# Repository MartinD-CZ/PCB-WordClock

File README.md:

# Simple PCB tabletop WordClock
*A relatively simple-to-make 100x100 mm WordClock made from 3 PCBs*

See [this article](http://embedblog.eu/?p=636) on my blog for more info.

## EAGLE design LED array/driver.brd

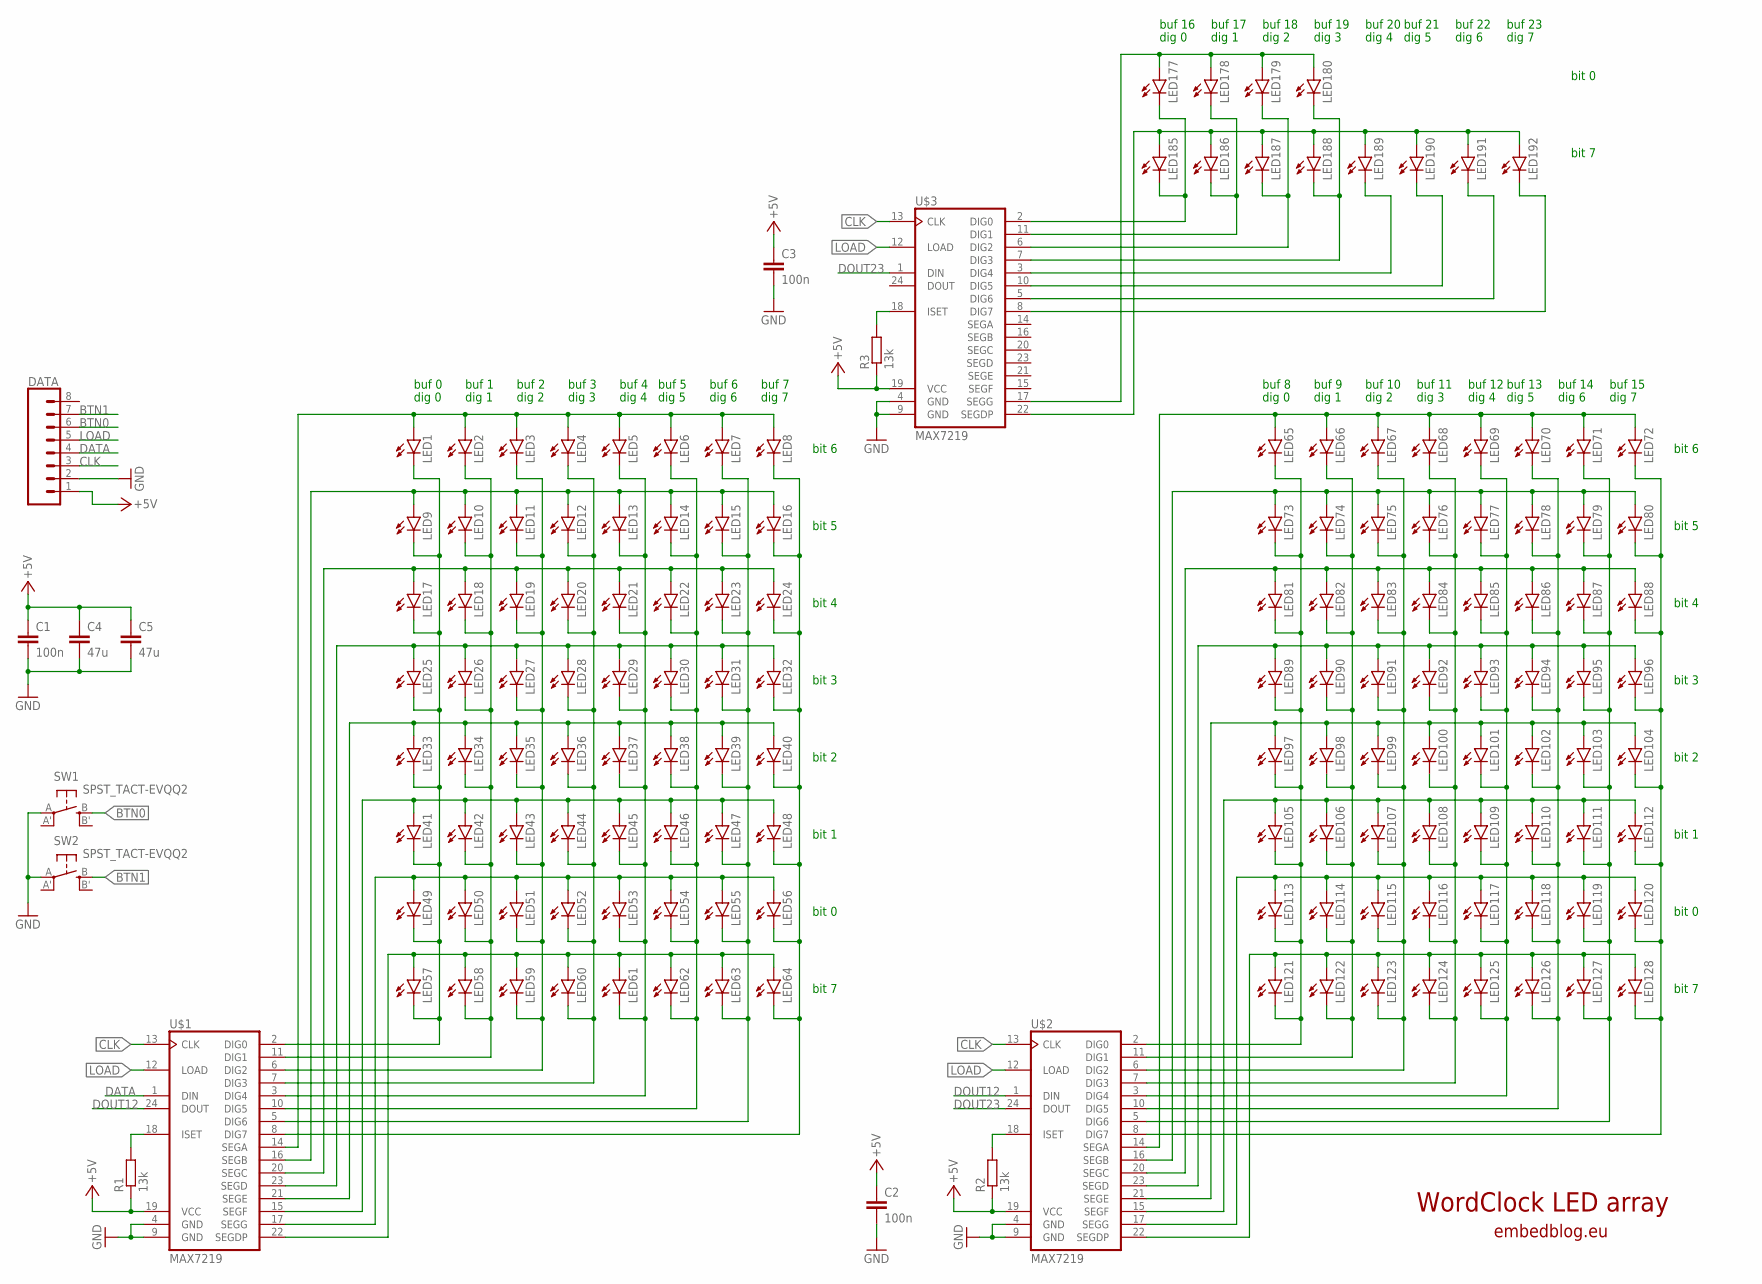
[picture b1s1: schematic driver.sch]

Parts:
C1, C2, C3: 100n; C1206
C4, C5: 47u; C1206
DATA: CONN_08"; 1X08
LED1, LED2, LED3, LED4, LED5, LED6, LED7, LED8, LED9, LED10, LED11, LED12, LED13, LED14, LED15, LED16, LED17, LED18, LED19, LED20, LED21, LED22, LED23, LED24, LED25, LED26, LED27, LED28, LED29, LED30, LED31, LED32, LED33, LED34, LED35, LED36, LED37, LED38, LED39, LED40, LED41, LED42, LED43, LED44, LED45, LED46, LED47, LED48, LED49, LED50, LED51, LED52, LED53, LED54, LED55, LED56, LED57, LED58, LED59, LED60, LED61, LED62, LED63, LED64, LED65, LED66, LED67, LED68, LED69, LED70, LED71, LED72, LED73, LED74, LED75, LED76, LED77, LED78, LED79, LED80, LED81, LED82, LED83, LED84, LED85, LED86, LED87, LED88, LED89, LED90, LED91, LED92, LED93, LED94, LED95, LED96, LED97, LED98, LED99, LED100, LED101, LED102, LED103, LED104, LED105, LED106, LED107, LED108, LED109, LED110, LED111, LED112, LED113, LED114, LED115, LED116, LED117, LED118, LED119, LED120, LED121, LED122, LED123, LED124, LED125, LED126, LED127, LED128, LED177, LED178, LED179, LED180, LED185, LED186, LED187, LED188, LED189, LED190, LED191, LED192: LEDCHIPLED_1206; CHIPLED_1206
R1, R2, R3: 13k; R1206
SW1, SW2: SPST_TACT-EVQQ2; EVQ-Q2
U$1, U$2, U$3: MAX7219; SO24W

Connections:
+5V: C1.1, C2.1, C3.1, C4.1, C5.1, DATA.1, R1.1, R2.1, R3.1, U$1.19 (VCC), U$2.19 (VCC), U$3.19 (VCC)
BTN0: DATA.6, SW1.B (S)
BTN1: DATA.7, SW2.B (S)
CLK: DATA.3, U$1.13 (CLK), U$2.13 (CLK), U$3.13 (CLK)
DATA: DATA.4, U$1.1 (DIN)
DOUT12: U$1.24 (DOUT), U$2.1 (DIN)
DOUT23: U$2.24 (DOUT), U$3.1 (DIN)
GND: C1.2, C2.2, C3.2, C4.2, C5.2, DATA.2, SW1.A, SW2.A, U$1.4 (GND), U$1.9 (GND), U$2.4 (GND), U$2.9 (GND), U$3.4 (GND), U$3.9 (GND)
LOAD: DATA.5, U$1.12 (LOAD), U$2.12 (LOAD), U$3.12 (LOAD)
unnamed: LED1.A, LED2.A, LED3.A, LED4.A, LED5.A, LED6.A, LED7.A, LED8.A, U$1.14 (SEGA)
unnamed: LED25.A, LED26.A, LED27.A, LED28.A, LED29.A, LED30.A, LED31.A, LED32.A, U$1.23 (SEGD)
unnamed: LED9.A, LED10.A, LED11.A, LED12.A, LED13.A, LED14.A, LED15.A, LED16.A, U$1.16 (SEGB)
unnamed: LED17.A, LED18.A, LED19.A, LED20.A, LED21.A, LED22.A, LED23.A, LED24.A, U$1.20 (SEGC)
unnamed: LED33.A, LED34.A, LED35.A, LED36.A, LED37.A, LED38.A, LED39.A, LED40.A, U$1.21 (SEGE)
unnamed: LED41.A, LED42.A, LED43.A, LED44.A, LED45.A, LED46.A, LED47.A, LED48.A, U$1.15 (SEGF)
unnamed: LED49.A, LED50.A, LED51.A, LED52.A, LED53.A, LED54.A, LED55.A, LED56.A, U$1.17 (SEGG)
unnamed: LED57.A, LED58.A, LED59.A, LED60.A, LED61.A, LED62.A, LED63.A, LED64.A, U$1.22 (SEGDP)
unnamed: LED1.C, LED9.C, LED17.C, LED25.C, LED33.C, LED41.C, LED49.C, LED57.C, U$1.2 (DIG0)
unnamed: R1.2, U$1.18 (ISET)
unnamed: LED65.A, LED66.A, LED67.A, LED68.A, LED69.A, LED70.A, LED71.A, LED72.A, U$2.14 (SEGA)
unnamed: LED73.A, LED74.A, LED75.A, LED76.A, LED77.A, LED78.A, LED79.A, LED80.A, U$2.16 (SEGB)
unnamed: LED81.A, LED82.A, LED83.A, LED84.A, LED85.A, LED86.A, LED87.A, LED88.A, U$2.20 (SEGC)
unnamed: LED89.A, LED90.A, LED91.A, LED92.A, LED93.A, LED94.A, LED95.A, LED96.A, U$2.23 (SEGD)
unnamed: LED97.A, LED98.A, LED99.A, LED100.A, LED101.A, LED102.A, LED103.A, LED104.A, U$2.21 (SEGE)
unnamed: LED105.A, LED106.A, LED107.A, LED108.A, LED109.A, LED110.A, LED111.A, LED112.A, U$2.15 (SEGF)
unnamed: LED2.C, LED10.C, LED18.C, LED26.C, LED34.C, LED42.C, LED50.C, LED58.C, U$1.11 (DIG1)
unnamed: LED113.A, LED114.A, LED115.A, LED116.A, LED117.A, LED118.A, LED119.A, LED120.A, U$2.17 (SEGG)
unnamed: LED121.A, LED122.A, LED123.A, LED124.A, LED125.A, LED126.A, LED127.A, LED128.A, U$2.22 (SEGDP)
unnamed: LED65.C, LED73.C, LED81.C, LED89.C, LED97.C, LED105.C, LED113.C, LED121.C, U$2.2 (DIG0)
unnamed: LED66.C, LED74.C, LED82.C, LED90.C, LED98.C, LED106.C, LED114.C, LED122.C, U$2.11 (DIG1)
unnamed: LED67.C, LED75.C, LED83.C, LED91.C, LED99.C, LED107.C, LED115.C, LED123.C, U$2.6 (DIG2)
unnamed: LED68.C, LED76.C, LED84.C, LED92.C, LED100.C, LED108.C, LED116.C, LED124.C, U$2.7 (DIG3)
unnamed: LED69.C, LED77.C, LED85.C, LED93.C, LED101.C, LED109.C, LED117.C, LED125.C, U$2.3 (DIG4)
unnamed: LED3.C, LED11.C, LED19.C, LED27.C, LED35.C, LED43.C, LED51.C, LED59.C, U$1.6 (DIG2)
unnamed: LED70.C, LED78.C, LED86.C, LED94.C, LED102.C, LED110.C, LED118.C, LED126.C, U$2.10 (DIG5)
unnamed: LED71.C, LED79.C, LED87.C, LED95.C, LED103.C, LED111.C, LED119.C, LED127.C, U$2.5 (DIG6)
unnamed: LED72.C, LED80.C, LED88.C, LED96.C, LED104.C, LED112.C, LED120.C, LED128.C, U$2.8 (DIG7)
unnamed: R2.2, U$2.18 (ISET)
unnamed: LED4.C, LED12.C, LED20.C, LED28.C, LED36.C, LED44.C, LED52.C, LED60.C, U$1.7 (DIG3)
unnamed: LED177.A, LED178.A, LED179.A, LED180.A, U$3.17 (SEGG)
unnamed: LED185.A, LED186.A, LED187.A, LED188.A, LED189.A, LED190.A, LED191.A, LED192.A, U$3.22 (SEGDP)
unnamed: LED177.C, LED185.C, U$3.2 (DIG0)
unnamed: LED178.C, LED186.C, U$3.11 (DIG1)
unnamed: LED5.C, LED13.C, LED21.C, LED29.C, LED37.C, LED45.C, LED53.C, LED61.C, U$1.3 (DIG4)
unnamed: LED179.C, LED187.C, U$3.6 (DIG2)
unnamed: LED180.C, LED188.C, U$3.7 (DIG3)
unnamed: LED189.C, U$3.3 (DIG4)
unnamed: LED190.C, U$3.10 (DIG5)
unnamed: LED191.C, U$3.5 (DIG6)
unnamed: LED192.C, U$3.8 (DIG7)
unnamed: R3.2, U$3.18 (ISET)
unnamed: LED6.C, LED14.C, LED22.C, LED30.C, LED38.C, LED46.C, LED54.C, LED62.C, U$1.10 (DIG5)
unnamed: LED7.C, LED15.C, LED23.C, LED31.C, LED39.C, LED47.C, LED55.C, LED63.C, U$1.5 (DIG6)
unnamed: LED8.C, LED16.C, LED24.C, LED32.C, LED40.C, LED48.C, LED56.C, LED64.C, U$1.8 (DIG7)

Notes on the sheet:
bit 0
bit 1
bit 2
bit 3
bit 4
bit 5
bit 6
bit 7
dig 0
dig 1
dig 2
dig 3
dig 4
dig 5
dig 6
dig 7
buf 0
buf 1
buf 2
buf 4
buf 5
buf 6
buf 7
buf 3
buf 8
buf 9
buf 10
buf 12
buf 13
buf 14
buf 15
buf 11
buf 16
buf 17
buf 18
buf 20
buf 21
buf 22
buf 23
buf 19

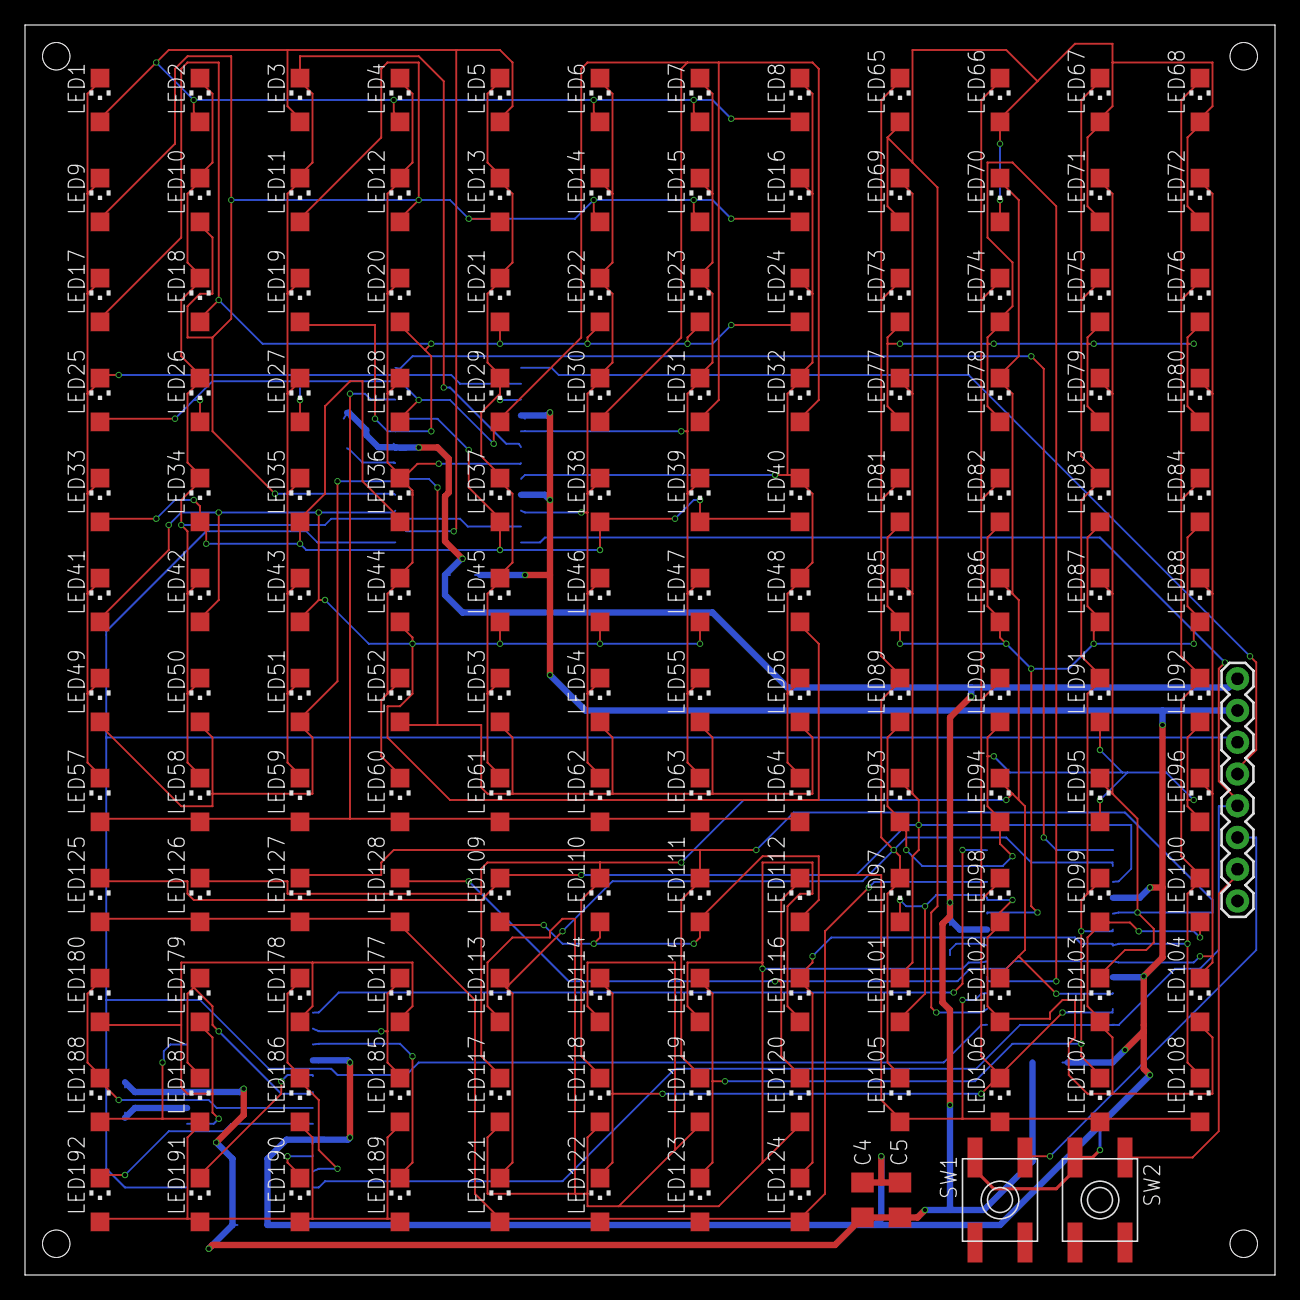
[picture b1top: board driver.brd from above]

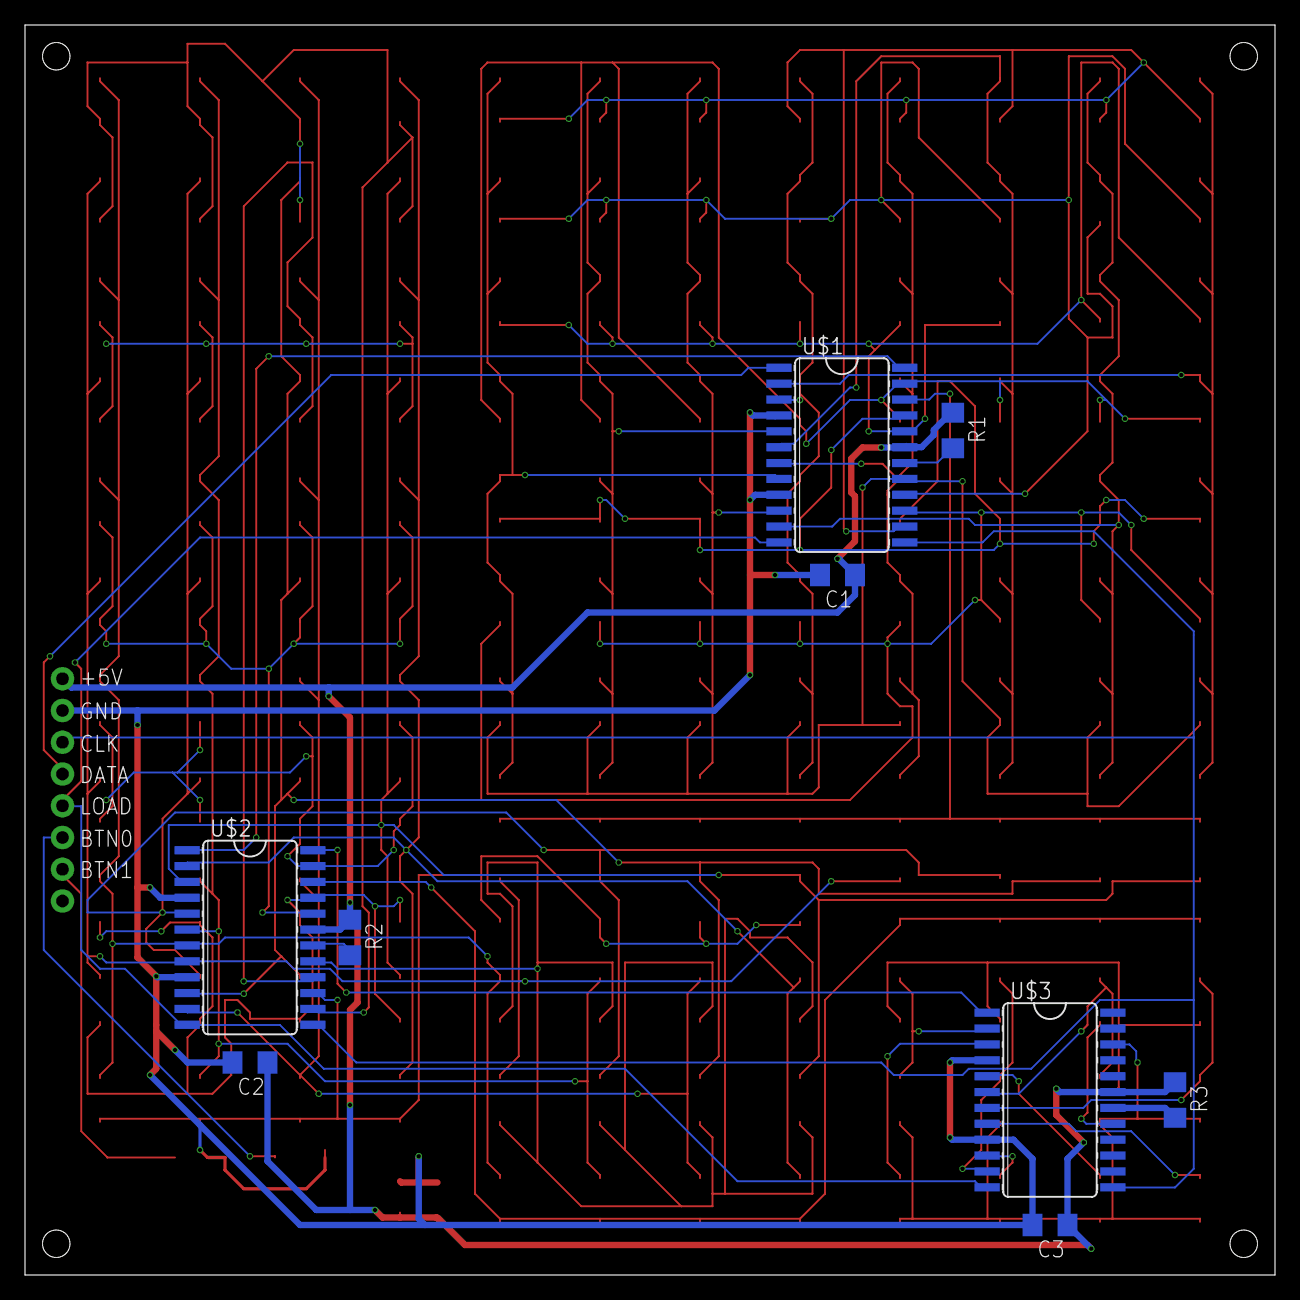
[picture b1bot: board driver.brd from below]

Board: 2 copper layers, 100.0 x 100.0 mm, 154 parts (9 on the bottom side), 54 nets.

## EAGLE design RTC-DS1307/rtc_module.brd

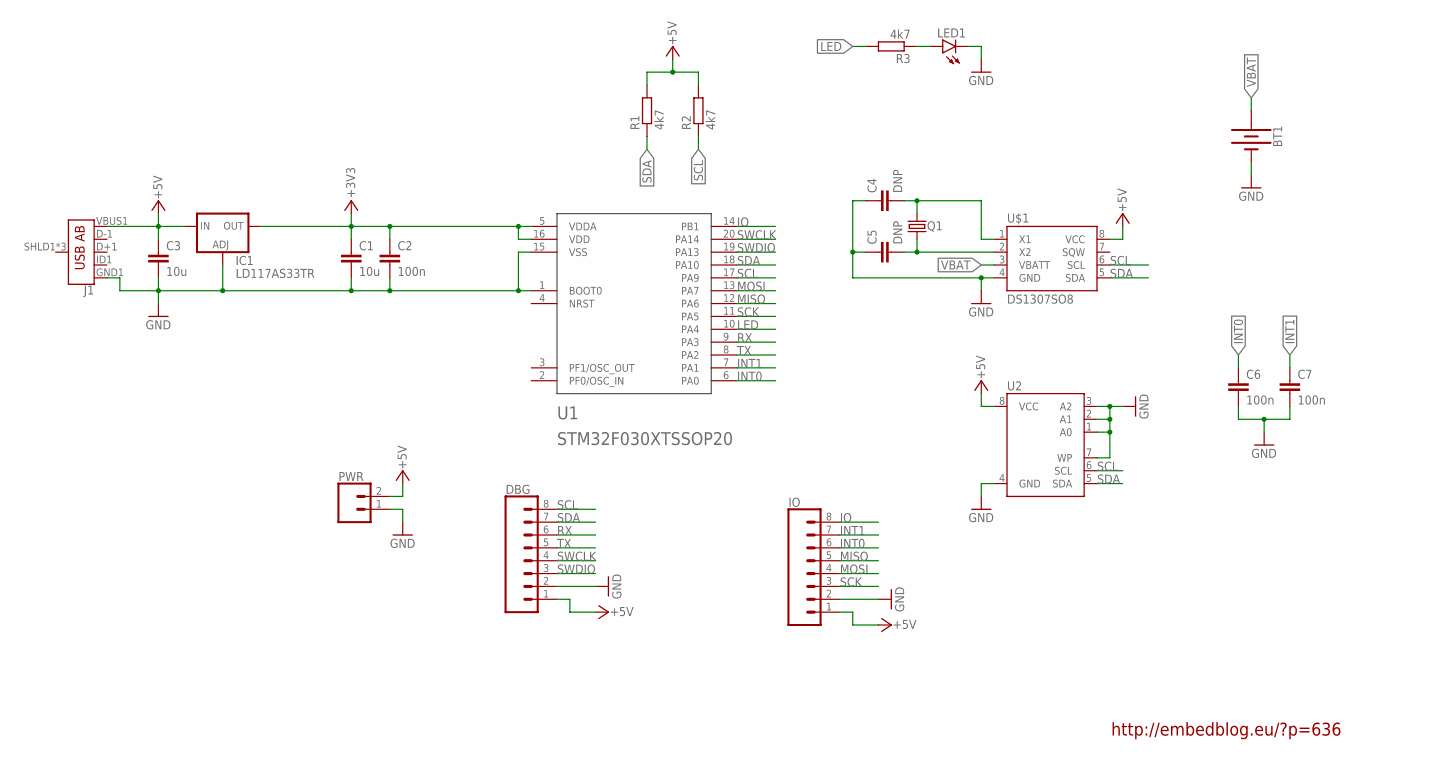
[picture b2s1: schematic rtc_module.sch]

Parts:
BT1: BATTERY-20MM_PTH; BATTCOM_20MM_PTH
C1, C3: 10u; C1206
C2, C6, C7: 100n; C1206
C4, C5: DNP; C1206
DBG: CONN_08"; 1X08
IC1: LD117AS33TR; SOT223
IO: CONN_08"; 1X08
J1: USB_AB_SMT; USB-AB-MICRO-SMD
LED1: LEDCHIPLED_1206; CHIPLED_1206
PWR: CONN_02PTH3; 1X02_LONGPADS
Q1: CRYSTALTC38H; TC38H
R1, R2, R3: 4k7; R1206
U1: STM32F030XTSSOP20; TSSOP-20
U2: 24LCXX; SOIC8
U$1: DS1307SO8; SO08

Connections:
+3V3: C1.1, C2.1, IC1.4 (OUT), U1.5 (VDDA), U1.16 (VDD)
+5V: C3.1, DBG.1, IC1.3 (IN), IO.1, J1.VBUS1 (VBUS), PWR.2, R1.2, R2.2, U2.8 (VCC), U$1.8 (VCC)
GND: BT1.2 (-), C1.2, C2.2, C3.2, C4.1, C5.1, C6.2, C7.2, DBG.2, IC1.1 (ADJ), IO.2, J1.GND1 (GND), LED1.C, PWR.1, U1.1 (BOOT0), U1.15 (VSS), U2.1 (A0), U2.2 (A1), U2.3 (A2), U2.4 (GND), U2.7 (WP), U$1.4 (GND)
INT0: C6.1, IO.6, U1.6 (PA0)
INT1: C7.1, IO.7, U1.7 (PA1)
IO: IO.8, U1.14 (PB1)
LED: R3.2, U1.10 (PA4)
MISO: IO.5, U1.12 (PA6)
MOSI: IO.4, U1.13 (PA7)
unnamed: C5.2, Q1.1, U$1.2 (X2)
unnamed: C4.2, Q1.2, U$1.1 (X1)
unnamed: LED1.A, R3.1
RX: DBG.6, U1.9 (PA3)
SCK: IO.3, U1.11 (PA5)
SCL: DBG.8, R2.1, U1.17 (PA9), U2.6 (SCL), U$1.6 (SCL)
SDA: DBG.7, R1.1, U1.18 (PA10), U2.5 (SDA), U$1.5 (SDA)
SWCLK: DBG.4, U1.20 (PA14)
SWDIO: DBG.3, U1.19 (PA13)
TX: DBG.5, U1.8 (PA2)
VBAT: BT1.1 (+), U$1.3 (VBATT)

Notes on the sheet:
http://embedblog.eu/?p=636

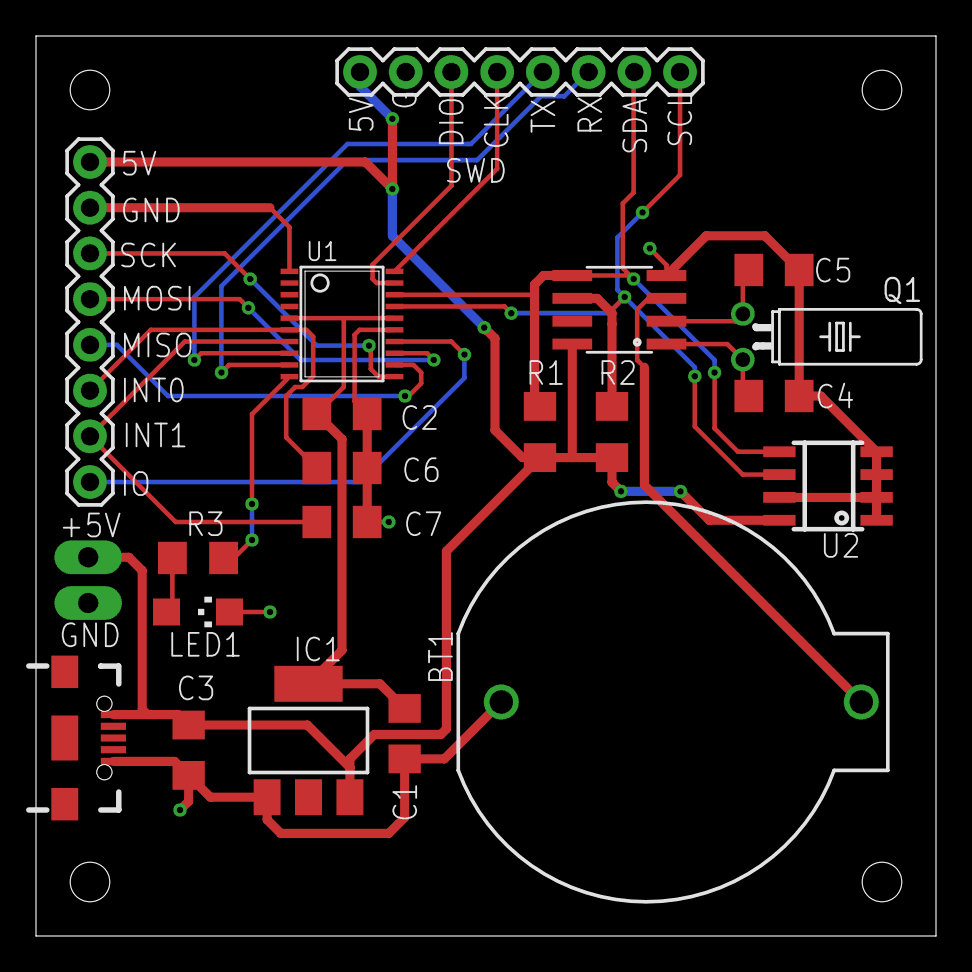
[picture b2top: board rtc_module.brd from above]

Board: 2 copper layers, 50.0 x 50.0 mm, 21 parts (0 on the bottom side), 20 nets.

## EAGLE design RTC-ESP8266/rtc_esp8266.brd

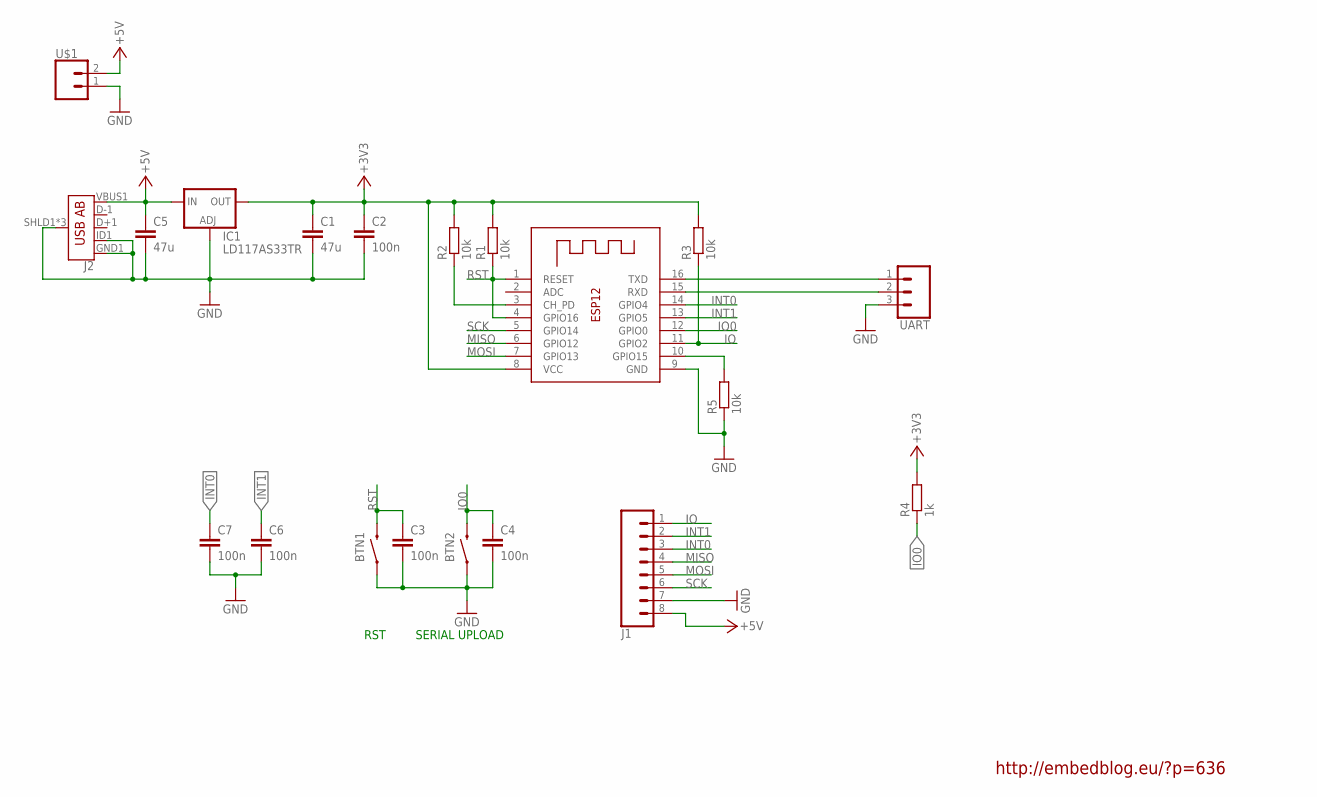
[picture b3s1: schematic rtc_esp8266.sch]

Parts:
BTN1, BTN2: MOMENTARY-SWITCH-SPST-SMD-5.2MM; TACTILE_SWITCH_SMD_5.2MM
C1, C5: 47u; C1206
C2, C3, C4, C6, C7: 100n; C1206
IC1: LD117AS33TR; SOT223
J1: CONN_08"; 1X08
J2: USB_AB_SMT; USB-AB-MICRO-SMD
R1, R2, R3, R5: 10k; R1206
R4: 1k; R1206
U$1: CONN_02PTH3; 1X02_LONGPADS
UART: 455-1750-1-ND; 1X03
X1: ESP-12

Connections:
+3V3: C1.1, C2.1, IC1.4 (OUT), R1.2, R2.2, R3.2, R4.2, X1.8 (VCC)
+5V: C5.1, IC1.3 (IN), J1.8, J2.VBUS1 (VBUS), U$1.2
GND: BTN1.1, BTN2.1, C1.2, C2.2, C3.2, C4.2, C5.2, C6.2, C7.2, IC1.1 (ADJ), J1.7, J2.GND1 (GND), J2.ID1 (USBID), J2.SHLD1 (SHIELD), J2.SHLD2 (SHIELD), J2.SHLD3 (SHIELD), R5.1, U$1.1, UART.3, X1.9 (GND)
INT0: C7.1, J1.3, X1.14 (GPIO4)
INT1: C6.1, J1.2, X1.13 (GPIO5)
IO: J1.1, R3.1, X1.11 (GPIO2)
IO0: BTN2.3 (2), C4.1, R4.1, X1.12 (GPIO0)
MISO: J1.4, X1.6 (GPIO12)
MOSI: J1.5, X1.7 (GPIO13)
unnamed: R2.1, X1.3 (CH_PD)
unnamed: R5.2, X1.10 (GPIO15)
RST: BTN1.3 (2), C3.1, R1.1, X1.1 (RESET), X1.4 (GPIO16)
RX: UART.2, X1.15 (RXD)
SCK: J1.6, X1.5 (GPIO14)
TX: UART.1, X1.16 (TXD)

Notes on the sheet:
RST
SERIAL UPLOAD
http://embedblog.eu/?p=636

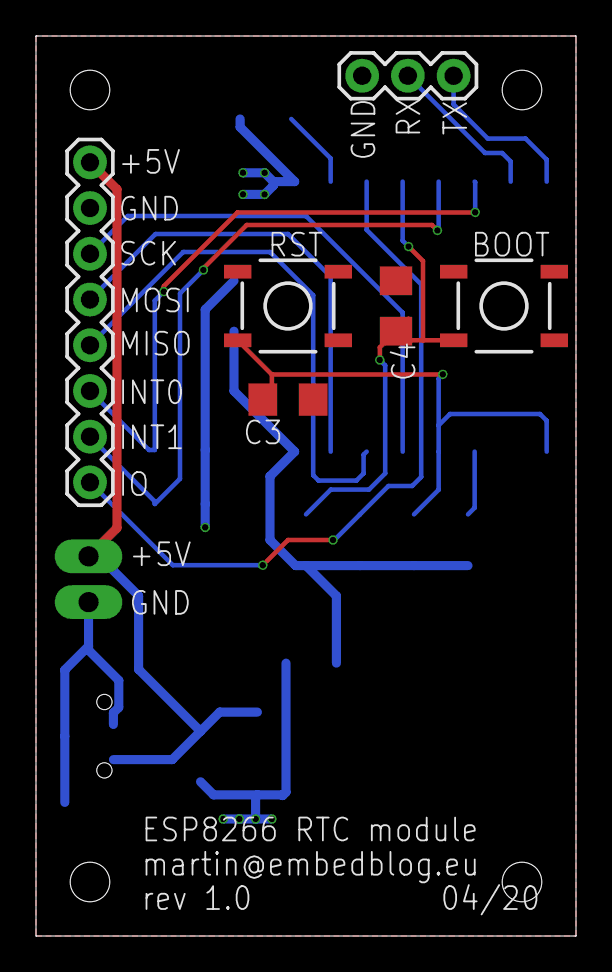
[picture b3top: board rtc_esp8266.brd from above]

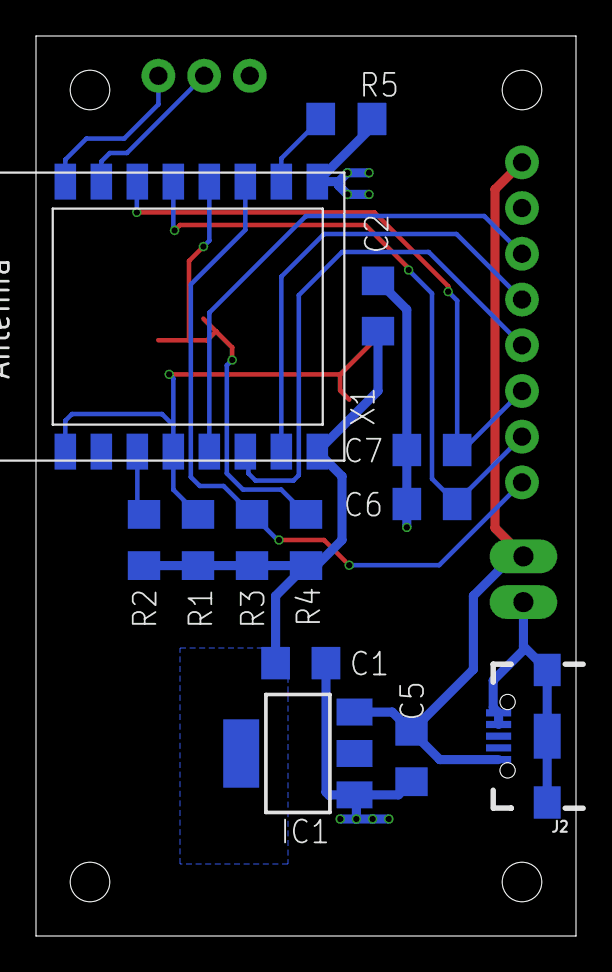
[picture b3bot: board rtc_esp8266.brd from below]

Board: 2 copper layers, 30.0 x 50.0 mm, 20 parts (13 on the bottom side), 15 nets.

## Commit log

2020-05-16 V1.0 - initial release

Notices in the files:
parts and their libraries:
SparkFun-Connectors: Licensing: Creative Commons ShareAlike 4.0 International - https://creativecommons.org/licenses/by-sa/4.0
m-pad-2.1: License : GNU General Public License version 2 (see bottom)
